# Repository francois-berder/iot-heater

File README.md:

# Connected heater

The architecture of this solution is as follows: a base station is running and parses incoming SMS. Each heater controller connects to the base station regularly and requests the current heater state.

## Base station

The base station is responsible for parsing incoming SMS that contains commands. It then keeps track of the heater state (off, eco, defrost...) and responds to requests.
It is based on a Raspberry Pi connected to a SIM5320E for cellular connection.

### Hardware

See `docs/base_station_assembly_guide.md` on how to assemble the base station.

### Software

The software is a daemon running on Linux. It communicates with smstools to send/receive SMS from a 3G module.
See `base_station/README.md` for more information.

## Heater controller (or IOT-heater)

Each electric heater can be controlled by sending a SMS to the base station. Heater controllers periodically connect to the base station to retrieve the current heater state.

Electric heaters are controlled by one wire:

See [here](https://www.planete-domotique.com/blog/2012/01/05/piloter-un-radiateur-grace-a-son-fil-pilote/) (in french) for more information on this control wire.

### Hardware

Heater controllers are built around a ESP8266 which controls two solid state relays. A small 220VAC to 5VDC module is used to power the ESP8266.
See Kicad files in folder `hardware` for more information.

See `docs/iot_heater_assembly_guide.md` for more information on how to assemble the heater controller.

### Firmware

The firmware is implemented using Arduino libraries for ESP8266.
See `heater_firmware/README.md` for more information.

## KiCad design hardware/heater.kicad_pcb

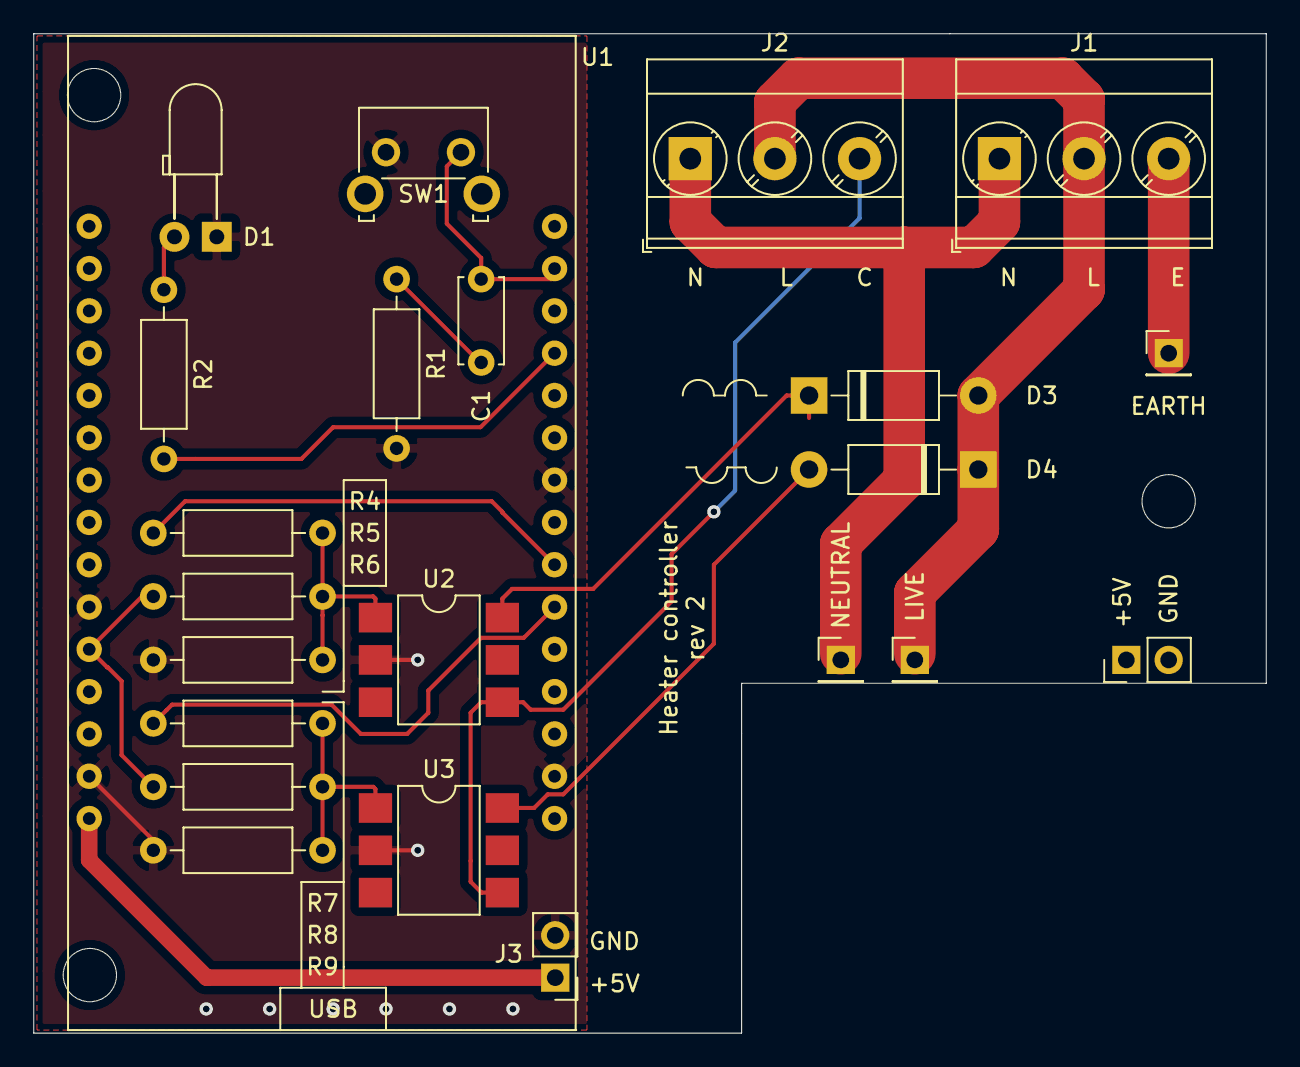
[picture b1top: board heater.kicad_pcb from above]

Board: 2 copper layers, 74.0 x 60.0 mm, 23 parts (0 on the bottom side), 17 nets.

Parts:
C1: 100nF; C_Disc_D5.0mm_W2.5mm_P5.00mm
D1: LED; LED_D3.0mm_Horizontal_O3.81mm_Z2.0mm
D3, D4: 1N4007; D_DO-41_SOD81_P10.16mm_Horizontal
J1, J2: Screw_Terminal_01x03; TerminalBlock_Phoenix_MKDS-3-3-5.08_1x03_P5.08mm_Horizontal
J3, J4: Conn_01x02_Female; PinHeader_1x02_P2.54mm_Vertical
J5, J6, J7: Conn_01x01_Female; PinHeader_1x01_P2.54mm_Vertical
R1, R2, R4, R7: 1k; R_Axial_DIN0207_L6.3mm_D2.5mm_P10.16mm_Horizontal
R5, R6, R8, R9: 10k; R_Axial_DIN0207_L6.3mm_D2.5mm_P10.16mm_Horizontal
SW1: SW_Push; SW_Tactile_SKHH_Angled
U1: NodeMCU_1.0_(ESP-12E); NodeMCU
U2, U3: CPC1972; SMDIP-6_W7.62mm

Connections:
+3V3: R5.1, R8.1, U1.11
+5V: J3.1, J4.1, U1.15
/EARTH: J1.3, J5.1
/LIVE: D3.2, D4.1, J1.2, J2.2, J6.1
/NEGATIVE_INPUT: R7.2, U1.21
/NEGATIVE_OUTPUT: J2.3, U2.4, U3.4
/NEUTRAL: J1.1, J2.1, J7.1
/POSITIVE_INPUT: R4.2, U1.22
/USER_BUTTON: C1.1, SW1.2, U1.29
GND: D1.1, J3.2, J4.2, R1.2, R6.2, R9.2, SW1.1, U1.10, U1.14, U1.17, U1.24, U2.2, U3.2
unnamed: C1.2, R1.1
unnamed: D1.2, R2.1
unnamed: D3.1, U2.6
unnamed: D4.2, U3.6
unnamed: R2.2, U1.27
unnamed: R4.1, R5.2, R6.1, U2.1
unnamed: R7.1, R8.2, R9.1, U3.1

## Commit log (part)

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2019-11-20 Spawn web server in uncommissioned state
2019-11-20 Initial import
2019-11-20 Blink LEDs in uncommissioned state
2019-11-20 Start Wifi AP in uncommissioned state
2019-11-20 Setup LEDs and button in commissioned state
2019-11-20 Initialize signal pins in commissionned state
2019-11-20 Spawn web server in commissionned state
2019-11-20 Erase settings if button is pressed for 10 seconds
2019-11-20 Add registration form for uncommissioned webpage
2019-12-15 Fix NodeMCU pins
2020-01-31 home_gateway: Add build instructions in readme
2020-01-31 home_gateway: Implement logger
2020-02-01 home_gateway: Implement basic device manager
2020-02-03 home_gateway: Improve logger
    * Limit log files to 1MB
    * Limit number of log files to 16MB
2020-02-09 home_gateway: Implement SMS server
2020-02-10 home_gateway: Implement PING command
2020-02-10 home_gateway: Implement verbose levels in sms_sender and commands in device manager
2020-02-10 home_gateway: Provide build information
2020-02-11 home_gateway: Rename DeviceManager to HomeGateway
2020-02-11 home_gateway: Implement main
2020-02-14 home_gateway: Fix setting BUILD_TIME and GIT_HASH
2020-02-14 home_gateway: Implement Logger:debug
2020-02-16 home_gateway: Fix Device::serialize
2020-03-02 Rename heater to heater_firmware
2020-03-04 home_gateway: Simplify device protocol
2020-03-06 home_gateway: Check that enough bytes were received before reading messages
2020-03-06 home_gateway: Simplify implementation - remove devices
2020-03-07 home_gateway: Load/save heater state to a file
2020-03-07 home_gateway: Trim SMS content
2020-03-07 home_gateway: Handle GET HEATER SMS
2020-03-07 home_gateway: Save state when heater state gets modified
2020-03-11 docs: Add info on control signal
2020-03-17 heater_firmware: Restart when pressing button for a long time
2020-03-17 heater_firmware: Connect to Wifi client during registration
2020-03-17 heater_firmware: Reduce settings name size to 32 characters
2020-03-17 heater_firmware: Save settings if registration is successful
2020-03-18 heater_firmware: Erase settings if button is pressed for a while
2020-03-18 heater_firmware: Check device name length
2020-03-18 heater_firmware: Restart device if it could not connect to Wifi network
2020-03-18 heater_firmware: Reduce name array size to 32
2020-03-19 heater_firmware: Add makefile
2020-03-20 heater_firmware: Blink fast while connecting to WiFi network
2020-03-20 heater_firmware: Fix BUTTON_PIN initialization in commissioned mode
2020-03-20 heater_firmware: Fix makefile dependencies
2020-03-20 heater_firmware: Produce binaries in bin folder
2020-03-21 heater_firmware: Add missing static qualifier
2020-03-21 heater_firmware: Do not initialize control pins in uncommissioned mode
2020-03-26 heater_firmware: Send ALIVE message every 30s
2020-03-26 heater_firmware: Turn off heater if it cannot connect to base station
2020-03-26 heater_firmware: Print heater state on web page
2020-03-30 home_gateway: Fix receiving data from devices
2020-03-30 heater_firmware: Read heater state reply
2020-03-30 heater_firmware: Send alive message immediately after being connected to wifi
2020-03-31 heater_firmware: Print git hash and build time during initialization
2020-03-31 heater_firmware: Fix base station hostname
2020-03-31 heater_firmware: Set hostname
2020-04-07 readme: Add instructions on how to build base station
2020-04-10 docs: Add schematics/datasheet
2020-04-10 Import heater hardware files
2020-04-11 Add base_station_installer script
2020-04-12 base_station: Implement GET IP SMS command
2020-04-12 heater_firmware: Describe LED status
2020-04-13 base_station: Implement GET HEATER HISTORY SMS command
2020-04-14 base_station: Describe all SMS commands
2020-04-15 base_station: Accept SMS from whitelist
2020-04-15 base_station: Confirm heater state over SMS
2020-04-19 base_station: Check phone number format
2020-04-19 base_station: Load/save phone whitelist to state file
2020-04-19 heater_firmware: Implement LED state in commissioned mode
2020-04-24 heater_firmware: Fix LED status once heater is connected to WiFi
2020-04-25 hardware: Design rev2 heater controller board
2020-04-25 heater_firmware: Fix status LED in commissioning mode
2020-04-25 heater_firmware: Decrease power consumption in commissioning mode
2020-04-29 base_station: Do not be case-sensitive for SMS commands
2020-04-29 heater_firmware: Use only one status LED
2020-04-29 base_station: Clarify response to GET HEATER HISTORY
2020-04-30 fixup! heater_firmware: Decrease power consumption in commissioning mode
2020-06-25 base_station: Implement HELP command
2020-06-25 base_station: Implement HEATER ON SMS command
2020-06-25 docs: Add diagram about control wire
2020-07-28 heater_firmware: Add documentation about reset button
2020-08-01 heater_firmware: Print ESP8266 chip ID upon startup
2020-12-10 Remove UPS pico hat
    Unfortunately , the UPS pico hat did not work very well and
    was constantly rebooting the Pi. The only way to fix this was to use
    a short USB cable. It would only work with a few 5V USB power
    supply.
2020-12-10 base_station_installer: Make sure installer does not build incorrectly silently
    Also, add some documentation to this script.
2020-12-10 base_station_installer: Add documentation to setup script
2020-12-10 docs: Add iot-heater assembly guide
2020-12-10 readme: Add reference to heater_firmware/readme
2020-12-12 base_station: Remove unused prototype
2020-12-20 Improve documentation
2020-12-20 base_station: Do not send empty SMS if public IP cannot be found
2020-12-22 base_station: Fix more cppcheck warnings
2020-12-22 docs: Add pull-down/pull-up resistors description
2020-12-30 base_station: Add emergency phone number feature
    Rename locked to m_locked.
    Add missing members initialization in constructor.
2020-12-30 base_station: Implement DEBUG WIFI command
2021-01-04 base_station: Implement message protocol v1
2021-01-04 docs: Rename base_station_protocol to message_protocol_specifications
2021-01-04 docs: Add message protocol specification
2021-01-04 base_station: Fix warnings and errors reported by clang
2021-01-04 base_station: Print warning if a device rebooted
2021-01-07 fixup! base_station: Implement message protocol v1
2021-01-10 fixup! base_station: Print warning if a device rebooted
2021-01-11 heater_firmware: Various improvements, fixes
    - Flash LED quickly if someone connected to Wifi AP
    - Add a bit of jitter to req state timer
    - Use default NTP server (pool.ntp.org)
    - Increase NTP update interval to 15min
    - Increase heater state request interval to 1min
    - Remove suffix to basestation hostname
2021-01-11 heater_firmware: Fix LED state in commissioning mode
    If everything is OK, then the LED should be the invert of
    the push button pin. This pin is tied high by a pull-up
    and pressing the button pulls this pin low.
2021-01-11 heater_firmware: Flash LED a few times before restarting after factory reset
2021-01-11 base_station: Fix printing MAC address in logs
    Add debug log when receiving heater state request.
2021-01-12 base_station: Refactor converting MAC addr array to string
2021-01-12 base_station: Refactor check state connections
2021-01-12 base_station: Check heater name
2021-01-13 heater_firmware: Build webpage only once in uncommssioned mode
2021-01-13 heater_firmware: Fix buffer overflow while building webpage
2021-01-13 heater_firmware: Check user-provided name and wifi SSID
2021-01-13 heater_firmware: Print device name on webpage
2021-01-13 heater_firmware: Fix resetting values when receiving heater state
2021-01-13 heater_firmware: Remove unnecessary variable
2021-01-14 heater_firmware: Check params before commissioning device
2021-01-14 heater_firmware: Specify base station hostname/IP address
2021-01-15 base_station: Implement web server to display status
2021-01-15 base_station: Mention libmicrohttpd dependency in readme
2021-01-18 base_station: Improve version
    - Print version upon startup
    - Add command line to print software version
2021-01-18 base_station: Implement DEBUG UPTIME command
2021-01-18 base_station: Print uptime on website
2021-01-18 heater_firmware: Add title to web pages
2021-01-20 base_station: Show 3G module connection on web page
2021-01-28 base_station: Communicate with 3G module to detect SIM card/network registration issues
2021-01-28 base_station: Periodically check 3G module presence
2021-01-28 heater_firmware: Show WiFi signal strength on webpage
2021-01-28 base_station_installer: Add arguments to specify branch and git repo url
2021-01-28 base_station: Reply if SMS command is invalid
2021-01-28 base_station: Fix non-periodic timers
2021-01-28 base_station: Show IP address on website
2021-01-28 base_station: Rename wifi_not_good_counter to wifi_error_counter
2021-01-29 base_station: Periodically check SMS daemon is running
2021-01-29 base_station_installer: Do not modify files if not necessary
2021-01-29 docs: Add user guide
2021-02-05 base_station_installer: Check for ssh-keygen
2021-02-07 base_station: Fix typo in uptime string
2021-02-07 heater_firmware: Fix version header filename
2021-02-07 heater_firmware: Fix commissioned source file name
2021-02-07 heater_firmware: Add missing file dependency in makefile
2021-02-07 heater_firmware: Add missing library dependencies
2021-02-07 heater_firmware: Explain how to install esp8266 board on Arduino-IDE
2021-02-07 heater_firmware: Mention Arduino IDE to compile project and flash board
2021-02-08 base_station: Fix timestamp format
2021-02-08 heater_firmware: Show last 5 errors on web page
2021-02-11 heater_firmware: Fix sending/receiving messages to base station
    write function does not always send the entire message in one call.
2021-02-17 heater_firmware: Improve reading message from WiFiClient
2021-02-19 base_station: Fix small typo in error message
2021-02-20 base_station: Fix reading message from socket
2021-02-20 heater_firmware: Fix error messages
2021-02-20 base_station: Log sending heater state reply failure/success
2021-02-24 [DEBUG]
2021-02-25 base_station: Fix starting stale timer
    Stale timer was not started so stale connections were never removed.
    Also, remove connection after 10 min idle time
2021-02-26 base_station: Fix warning message if device rebooted
2021-03-01 base_station: Increase threshold to 100 for detecting device reboots
    During testing, it appeared that the base station would fail to receive
    a request from a device several times in a row.
    To lower the amount of false positive, let's increase the threshold from
    3 to 100.
2021-03-01 base_station: Immediately close socket fd if no callback set
2021-10-01 base_station_installer: Block UK phone numbers
2021-10-01 base_station: Set country code to FR in wpa_supplicant.conf
2021-10-01 docs: user_guide: Add minor details/fixes
2021-10-01 heater_firmware: Fix makefile
2021-10-01 heater_firmware: Specify esp8266 board version
2021-11-16 base_station: Fix warnings reported by clang static analyzer
2021-12-06 base_station: Fix typo
2021-12-06 base_station: Clean SMS outgoing directory upon boot
2021-12-10 base_station: Use C++ std library to generate a random number
2021-12-10 base_station_installer: Remove installing unnecessary packages
2022-05-09 heater_firmware: Fix printing uptime in non commissioned mode
2022-05-11 base_station: Return boolean if SMS was sent or not
